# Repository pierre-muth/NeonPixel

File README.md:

# NeonPixel
Files about the NeonPixel Matrix, made of chainable 5V neon INS-1 bulbs

Detail here https://pierremuth.wordpress.com/2020/07/08/neon-pixel/

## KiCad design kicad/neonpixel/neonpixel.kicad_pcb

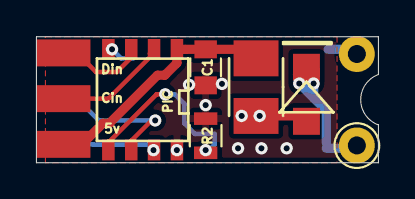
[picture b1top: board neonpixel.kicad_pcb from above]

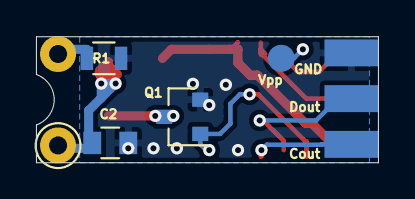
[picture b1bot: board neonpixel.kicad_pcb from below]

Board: 2 copper layers, 19.0 x 7.0 mm, 12 parts (5 on the bottom side), 11 nets.

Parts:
C1: 100n; C_0805
C2: 1n; C_0805
D1: D_Schottky; SMD_Diode
J1: Conn_01x02_Female; NeonPins
J2, J3: Conn_01x03_Female; SMD_3_pin_254
J4: Conn_01x01_Female; SMD_pad
L1: 10uH; SMD_inductor
PIC: PIC16F15313; SOIC-8-N
Q1: BSS138; SOT-23
R1: 10K; R_0805
R2: 100K; R_0805

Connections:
+5V: C1.1, J2.1, L1.1, PIC.1
/SCKin: J2.2, PIC.2
/SCKout: J3.3, PIC.7
/SDAin: J2.3, PIC.3
/SDAout: J3.2, PIC.6
/Vpp: J4.1, PIC.4
GND: C1.2, C2.2, J3.1, PIC.8, Q1.2, R1.2, R2.2
unnamed: C2.1, D1.1, J1.1
unnamed: D1.2, L1.2, Q1.3
unnamed: J1.2, R1.1
unnamed: PIC.5, Q1.1, R2.1

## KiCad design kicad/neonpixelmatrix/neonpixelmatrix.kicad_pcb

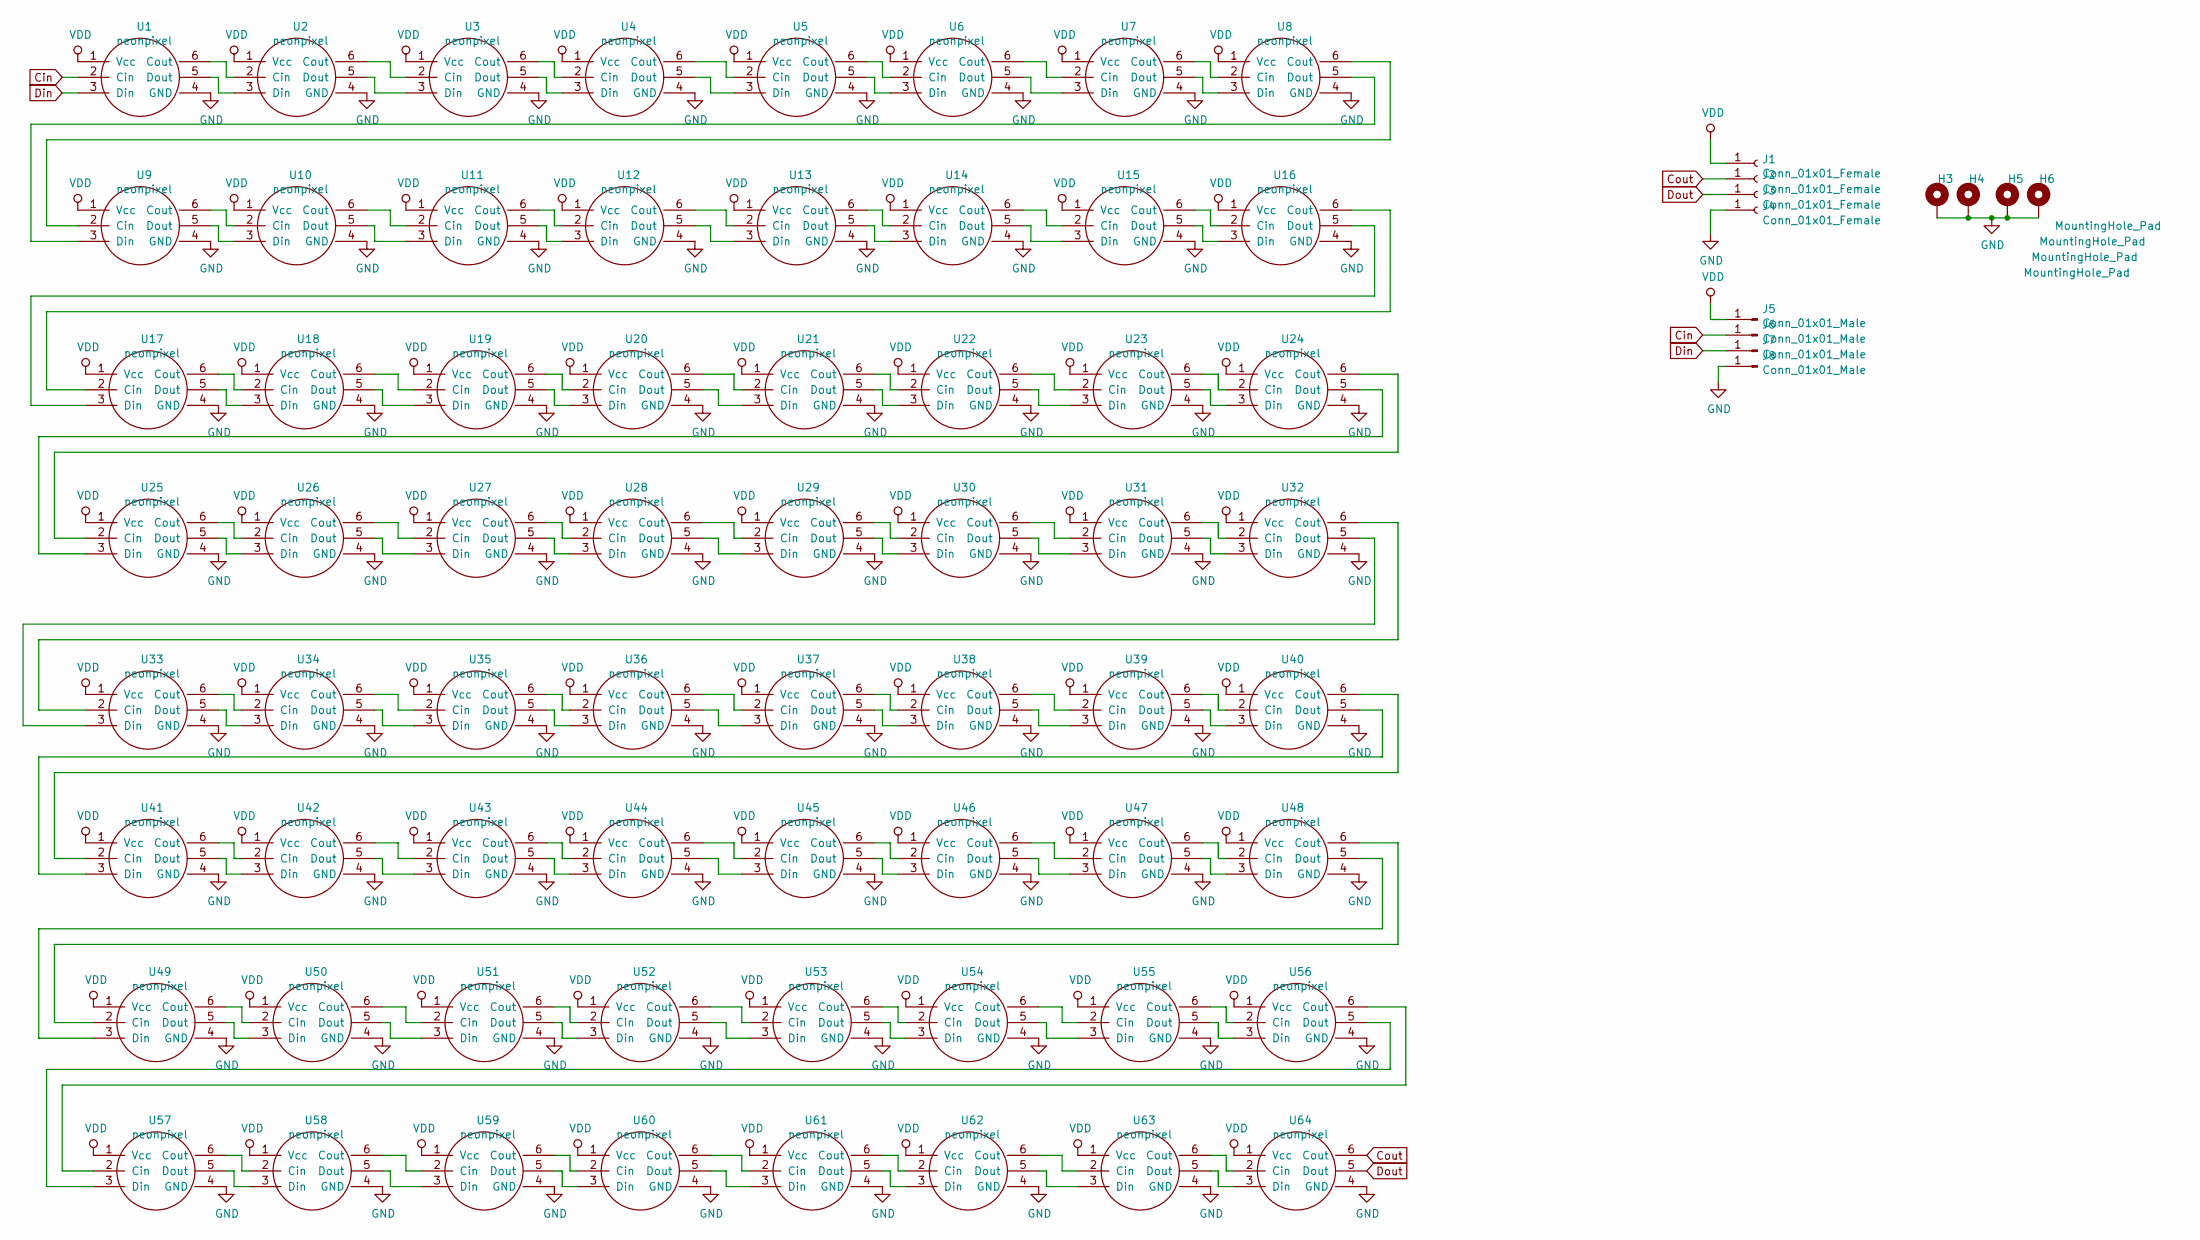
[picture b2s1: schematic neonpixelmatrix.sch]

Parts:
H3, H4, H5, H6: MountingHole_Pad; mountingM2
J1, J2, J3, J4: Conn_01x01_Female; Pin_Header_Straight_1x01_Pitch2.54mm
J5, J6, J7, J8: Conn_01x01_Male; Pin_Header_Straight_1x01_Pitch2.54mm
U1, U2, U3, U4, U5, U6, U7, U8, U9, U10, U11, U12, U13, U14, U15, U16, U17, U18, U19, U20, U21, U22, U23, U24, U25, U26, U27, U28, U29, U30, U31, U32, U33, U34, U35, U36, U37, U38, U39, U40, U41, U42, U43, U44, U45, U46, U47, U48, U49, U50, U51, U52, U53, U54, U55, U56, U57, U58, U59, U60, U61, U62, U63, U64: neonpixel

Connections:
Cin: J6.1, U1.2 (Cin)
Cout: J2.1, U64.6 (Cout)
Din: J7.1, U1.3 (Din)
Dout: J3.1, U64.5 (Dout)
GND: H3.1, H4.1, H5.1, H6.1, J4.1, J8.1, U1.4 (GND), U2.4 (GND), U3.4 (GND), U4.4 (GND), U5.4 (GND), U6.4 (GND), U7.4 (GND), U8.4 (GND), U9.4 (GND), U10.4 (GND), U11.4 (GND), U12.4 (GND), U13.4 (GND), U14.4 (GND), U15.4 (GND), U16.4 (GND), U17.4 (GND), U18.4 (GND), U19.4 (GND), U20.4 (GND), U21.4 (GND), U22.4 (GND), U23.4 (GND), U24.4 (GND), U25.4 (GND), U26.4 (GND), U27.4 (GND), U28.4 (GND), U29.4 (GND), U30.4 (GND), U31.4 (GND), U32.4 (GND), U33.4 (GND), U34.4 (GND), U35.4 (GND), U36.4 (GND), U37.4 (GND), U38.4 (GND), U39.4 (GND), U40.4 (GND), U41.4 (GND), U42.4 (GND), U43.4 (GND), U44.4 (GND), U45.4 (GND), U46.4 (GND), U47.4 (GND), U48.4 (GND), U49.4 (GND), U50.4 (GND), U51.4 (GND), U52.4 (GND), U53.4 (GND), U54.4 (GND), U55.4 (GND), U56.4 (GND), U57.4 (GND), U58.4 (GND), U59.4 (GND), U60.4 (GND), U61.4 (GND), U62.4 (GND), U63.4 (GND), U64.4 (GND)
unnamed: U1.5 (Dout), U2.3 (Din)
unnamed: U1.6 (Cout), U2.2 (Cin)
unnamed: U2.5 (Dout), U3.3 (Din)
unnamed: U2.6 (Cout), U3.2 (Cin)
unnamed: U3.5 (Dout), U4.3 (Din)
unnamed: U3.6 (Cout), U4.2 (Cin)
unnamed: U4.5 (Dout), U5.3 (Din)
unnamed: U4.6 (Cout), U5.2 (Cin)
unnamed: U5.5 (Dout), U6.3 (Din)
unnamed: U5.6 (Cout), U6.2 (Cin)
unnamed: U6.5 (Dout), U7.3 (Din)
unnamed: U6.6 (Cout), U7.2 (Cin)
unnamed: U7.5 (Dout), U8.3 (Din)
unnamed: U7.6 (Cout), U8.2 (Cin)
unnamed: U8.5 (Dout), U9.3 (Din)
unnamed: U8.6 (Cout), U9.2 (Cin)
unnamed: U9.6 (Cout), U10.2 (Cin)
unnamed: U9.5 (Dout), U10.3 (Din)
unnamed: U10.5 (Dout), U11.3 (Din)
unnamed: U10.6 (Cout), U11.2 (Cin)
unnamed: U11.5 (Dout), U12.3 (Din)
unnamed: U11.6 (Cout), U12.2 (Cin)
unnamed: U12.5 (Dout), U13.3 (Din)
unnamed: U12.6 (Cout), U13.2 (Cin)
unnamed: U13.5 (Dout), U14.3 (Din)
unnamed: U13.6 (Cout), U14.2 (Cin)
unnamed: U14.5 (Dout), U15.3 (Din)
unnamed: U14.6 (Cout), U15.2 (Cin)
unnamed: U15.5 (Dout), U16.3 (Din)
unnamed: U15.6 (Cout), U16.2 (Cin)
unnamed: U16.5 (Dout), U17.3 (Din)
unnamed: U16.6 (Cout), U17.2 (Cin)
unnamed: U17.5 (Dout), U18.3 (Din)
unnamed: U17.6 (Cout), U18.2 (Cin)
unnamed: U18.5 (Dout), U19.3 (Din)
unnamed: U18.6 (Cout), U19.2 (Cin)
unnamed: U19.5 (Dout), U20.3 (Din)
unnamed: U19.6 (Cout), U20.2 (Cin)
unnamed: U20.5 (Dout), U21.3 (Din)
unnamed: U20.6 (Cout), U21.2 (Cin)
unnamed: U21.5 (Dout), U22.3 (Din)
unnamed: U21.6 (Cout), U22.2 (Cin)
unnamed: U22.5 (Dout), U23.3 (Din)
unnamed: U22.6 (Cout), U23.2 (Cin)
unnamed: U23.5 (Dout), U24.3 (Din)
unnamed: U23.6 (Cout), U24.2 (Cin)
unnamed: U24.5 (Dout), U25.3 (Din)
unnamed: U24.6 (Cout), U25.2 (Cin)
unnamed: U25.5 (Dout), U26.3 (Din)
unnamed: U25.6 (Cout), U26.2 (Cin)
unnamed: U26.5 (Dout), U27.3 (Din)
unnamed: U26.6 (Cout), U27.2 (Cin)
unnamed: U27.5 (Dout), U28.3 (Din)
unnamed: U27.6 (Cout), U28.2 (Cin)
unnamed: U28.5 (Dout), U29.3 (Din)
unnamed: U28.6 (Cout), U29.2 (Cin)
unnamed: U29.5 (Dout), U30.3 (Din)
unnamed: U29.6 (Cout), U30.2 (Cin)
unnamed: U30.5 (Dout), U31.3 (Din)
unnamed: U30.6 (Cout), U31.2 (Cin)
unnamed: U31.5 (Dout), U32.3 (Din)
unnamed: U31.6 (Cout), U32.2 (Cin)
unnamed: U32.5 (Dout), U33.3 (Din)
unnamed: U32.6 (Cout), U33.2 (Cin)
unnamed: U33.5 (Dout), U34.3 (Din)
unnamed: U33.6 (Cout), U34.2 (Cin)
unnamed: U34.5 (Dout), U35.3 (Din)
unnamed: U34.6 (Cout), U35.2 (Cin)
unnamed: U35.5 (Dout), U36.3 (Din)
unnamed: U35.6 (Cout), U36.2 (Cin)
unnamed: U36.5 (Dout), U37.3 (Din)
unnamed: U36.6 (Cout), U37.2 (Cin)
unnamed: U37.5 (Dout), U38.3 (Din)
unnamed: U37.6 (Cout), U38.2 (Cin)
unnamed: U38.5 (Dout), U39.3 (Din)
unnamed: U38.6 (Cout), U39.2 (Cin)
unnamed: U39.5 (Dout), U40.3 (Din)
unnamed: U39.6 (Cout), U40.2 (Cin)
unnamed: U40.5 (Dout), U41.3 (Din)
unnamed: U40.6 (Cout), U41.2 (Cin)
unnamed: U41.5 (Dout), U42.3 (Din)
unnamed: U41.6 (Cout), U42.2 (Cin)
unnamed: U42.5 (Dout), U43.3 (Din)
unnamed: U42.6 (Cout), U43.2 (Cin)
unnamed: U43.5 (Dout), U44.3 (Din)
unnamed: U43.6 (Cout), U44.2 (Cin)
unnamed: U44.5 (Dout), U45.3 (Din)
unnamed: U44.6 (Cout), U45.2 (Cin)
unnamed: U45.5 (Dout), U46.3 (Din)
unnamed: U45.6 (Cout), U46.2 (Cin)
unnamed: U46.5 (Dout), U47.3 (Din)
unnamed: U46.6 (Cout), U47.2 (Cin)
unnamed: U47.5 (Dout), U48.3 (Din)
unnamed: U47.6 (Cout), U48.2 (Cin)
unnamed: U48.5 (Dout), U49.3 (Din)
unnamed: U48.6 (Cout), U49.2 (Cin)
unnamed: U49.5 (Dout), U50.3 (Din)
unnamed: U49.6 (Cout), U50.2 (Cin)
unnamed: U50.5 (Dout), U51.3 (Din)
unnamed: U50.6 (Cout), U51.2 (Cin)
unnamed: U51.5 (Dout), U52.3 (Din)
unnamed: U51.6 (Cout), U52.2 (Cin)
unnamed: U52.5 (Dout), U53.3 (Din)
unnamed: U52.6 (Cout), U53.2 (Cin)
unnamed: U53.5 (Dout), U54.3 (Din)
unnamed: U53.6 (Cout), U54.2 (Cin)
unnamed: U54.5 (Dout), U55.3 (Din)
unnamed: U54.6 (Cout), U55.2 (Cin)
unnamed: U55.5 (Dout), U56.3 (Din)
unnamed: U55.6 (Cout), U56.2 (Cin)
unnamed: U56.5 (Dout), U57.3 (Din)
unnamed: U56.6 (Cout), U57.2 (Cin)
unnamed: U57.5 (Dout), U58.3 (Din)
unnamed: U57.6 (Cout), U58.2 (Cin)
unnamed: U58.5 (Dout), U59.3 (Din)
unnamed: U58.6 (Cout), U59.2 (Cin)
unnamed: U59.5 (Dout), U60.3 (Din)
unnamed: U59.6 (Cout), U60.2 (Cin)
unnamed: U60.5 (Dout), U61.3 (Din)
unnamed: U60.6 (Cout), U61.2 (Cin)
unnamed: U61.5 (Dout), U62.3 (Din)
unnamed: U61.6 (Cout), U62.2 (Cin)
unnamed: U62.5 (Dout), U63.3 (Din)
unnamed: U62.6 (Cout), U63.2 (Cin)
unnamed: U63.5 (Dout), U64.3 (Din)
unnamed: U63.6 (Cout), U64.2 (Cin)
VDD: J1.1, J5.1, U1.1 (Vcc), U2.1 (Vcc), U3.1 (Vcc), U4.1 (Vcc), U5.1 (Vcc), U6.1 (Vcc), U7.1 (Vcc), U8.1 (Vcc), U9.1 (Vcc), U10.1 (Vcc), U11.1 (Vcc), U12.1 (Vcc), U13.1 (Vcc), U14.1 (Vcc), U15.1 (Vcc), U16.1 (Vcc), U17.1 (Vcc), U18.1 (Vcc), U19.1 (Vcc), U20.1 (Vcc), U21.1 (Vcc), U22.1 (Vcc), U23.1 (Vcc), U24.1 (Vcc), U25.1 (Vcc), U26.1 (Vcc), U27.1 (Vcc), U28.1 (Vcc), U29.1 (Vcc), U30.1 (Vcc), U31.1 (Vcc), U32.1 (Vcc), U33.1 (Vcc), U34.1 (Vcc), U35.1 (Vcc), U36.1 (Vcc), U37.1 (Vcc), U38.1 (Vcc), U39.1 (Vcc), U40.1 (Vcc), U41.1 (Vcc), U42.1 (Vcc), U43.1 (Vcc), U44.1 (Vcc), U45.1 (Vcc), U46.1 (Vcc), U47.1 (Vcc), U48.1 (Vcc), U49.1 (Vcc), U50.1 (Vcc), U51.1 (Vcc), U52.1 (Vcc), U53.1 (Vcc), U54.1 (Vcc), U55.1 (Vcc), U56.1 (Vcc), U57.1 (Vcc), U58.1 (Vcc), U59.1 (Vcc), U60.1 (Vcc), U61.1 (Vcc), U62.1 (Vcc), U63.1 (Vcc), U64.1 (Vcc)

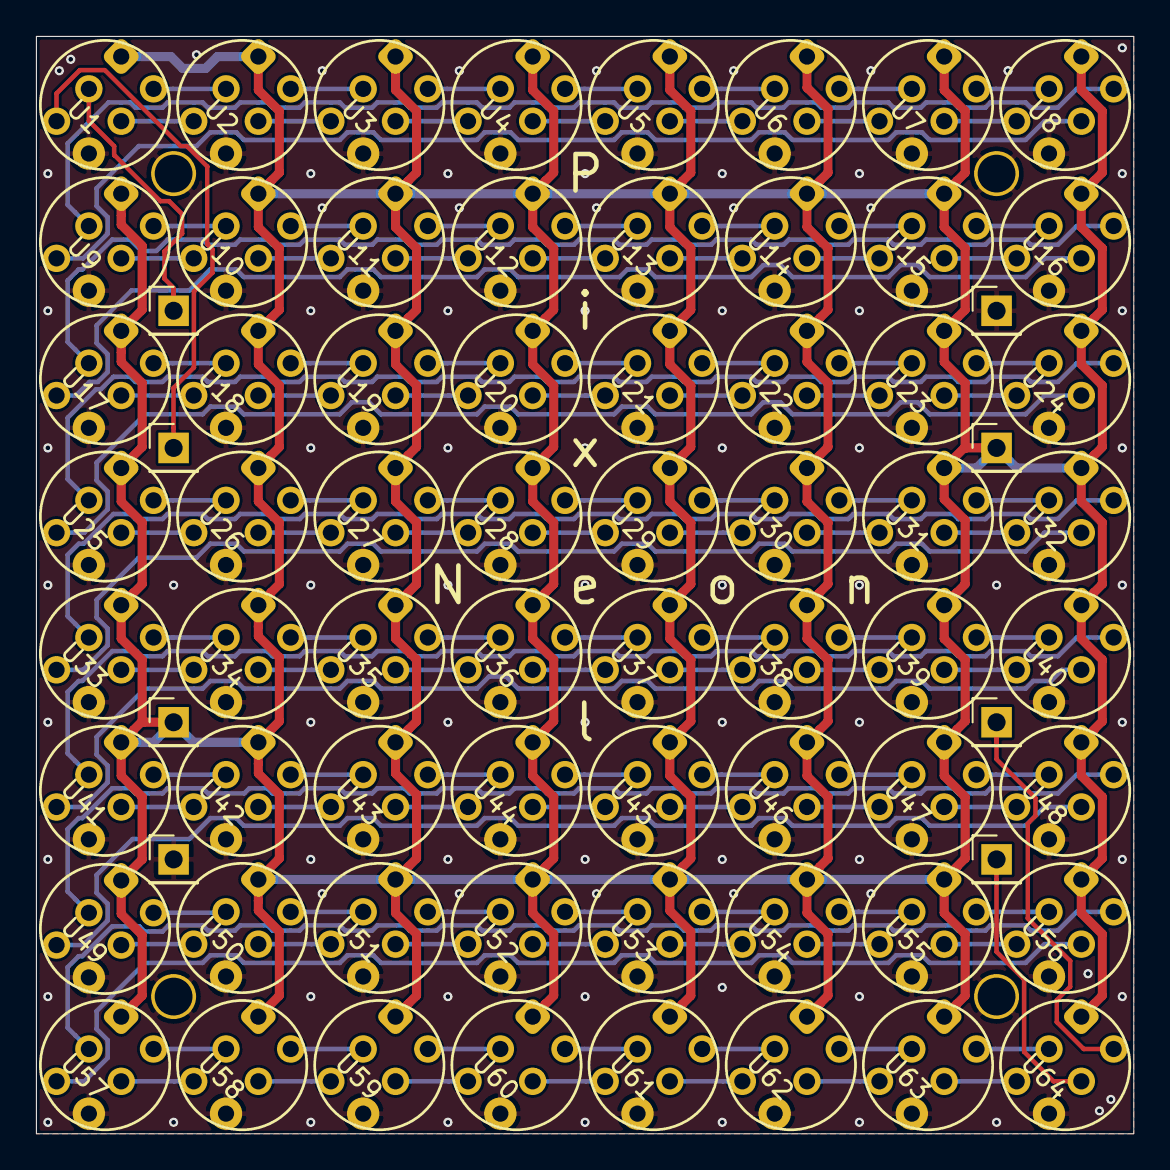
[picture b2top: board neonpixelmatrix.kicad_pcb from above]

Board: 2 copper layers, 61.0 x 61.0 mm, 76 parts (0 on the bottom side), 132 nets.

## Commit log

2020-07-14 Muth Font from www.pentacom.jp
    Muth Font from http://www.pentacom.jp/pentacom/bitfontmaker2/
2020-07-18 adding pictures
2020-08-11 Adding MPLAB project files of the PIC16F15313s
2021-03-10 upload socket screen connection ESP32 code
2021-03-10 Java code to stream video to ESP32 socket via wifi
